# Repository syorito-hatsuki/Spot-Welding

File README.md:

# Spot Welding

## Description
Simple Arduino spot welding controller

## Requirements
* [VSCode](https://code.visualstudio.com)
* [PlatformIO Extension](https://marketplace.visualstudio.com/items?itemName=platformio.platformio-ide)

## Structure 
* `.vscode - Visual Studio Code configs for current project`
* `include - PlatformIO folder for C++ header files`
* `lib - PlatformIO folder for downloaded libraries`
* `pcb - KiCAD files (schematic, pcb, components)`
* `src - Source code for Arduino`
* `test - Unit test folder`

## Licence
[MIT License](https://github.com/syorito-hatsuki/Spot-Welding/blob/master/LICENSE)

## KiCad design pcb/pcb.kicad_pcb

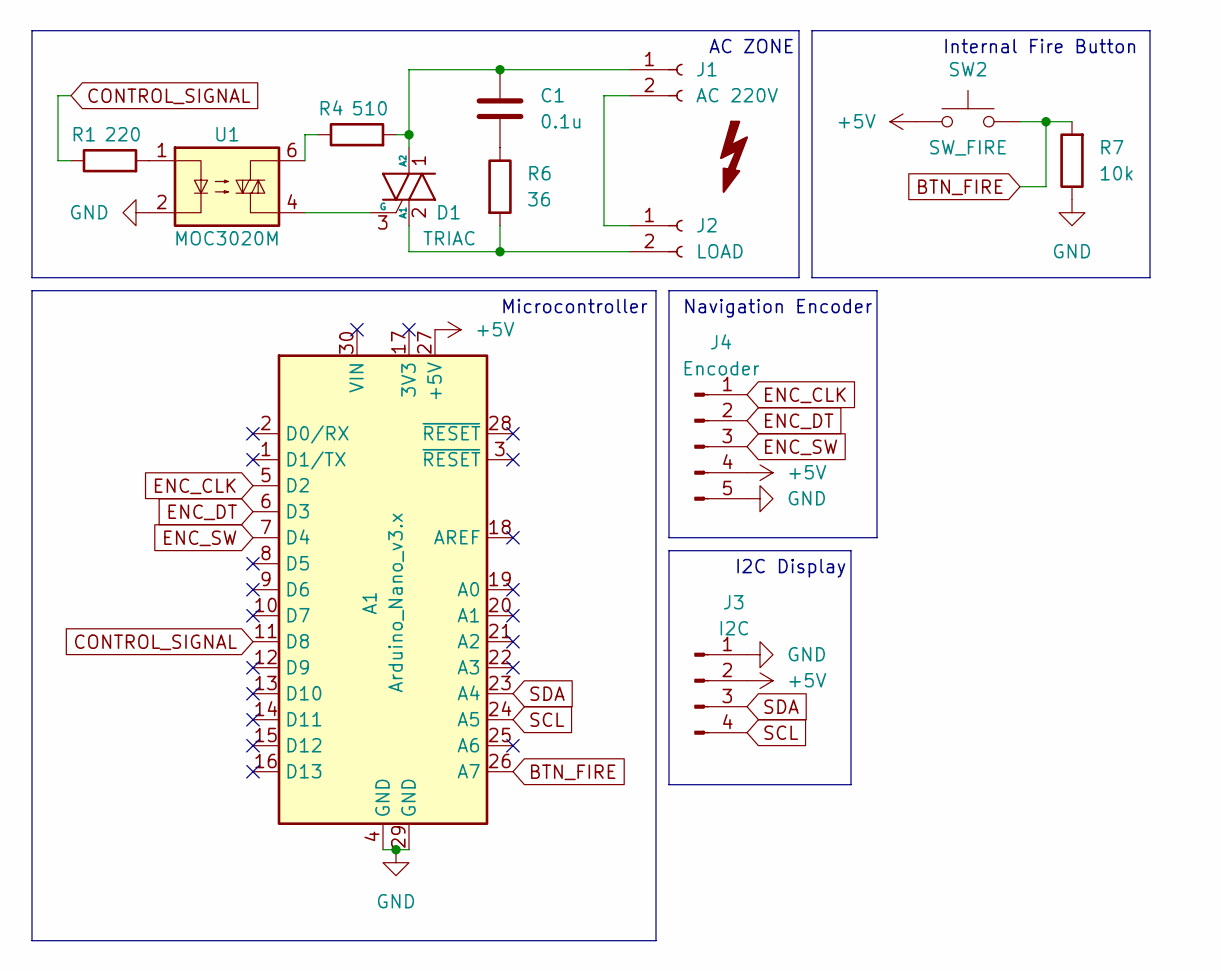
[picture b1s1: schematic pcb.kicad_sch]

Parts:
A1: Arduino_Nano_v3.x; Arduino_Nano
C1: 0.1u; C_Rect_L18.0mm_W6.0mm_P15.00mm_FKS3_FKP3
D1: TRIAC; TO-220-3_Vertical
J1: AC 220V; TerminalBlock_bornier-2_P5.08mm
J2: LOAD; TerminalBlock_bornier-2_P5.08mm
J3: I2C; PinHeader_1x04_P2.54mm_Vertical
J4: Encoder; PinHeader_1x05_P2.54mm_Vertical
R1: 220; R_Axial_DIN0207_L6.3mm_D2.5mm_P10.16mm_Horizontal
R4: 510; R_Axial_DIN0207_L6.3mm_D2.5mm_P10.16mm_Horizontal
R6: 36; R_Axial_DIN0207_L6.3mm_D2.5mm_P10.16mm_Horizontal
R7: 10k; R_Axial_DIN0207_L6.3mm_D2.5mm_P10.16mm_Horizontal
SW2: SW_FIRE; PinHeader_1x02_P2.54mm_Vertical
U1: MOC3020M; DIP-6_W7.62mm_LongPads

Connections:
+5V: A1.27 (+5V), J3.2, J4.4, SW2.1
BTN_FIRE: A1.26 (A7), R7.2, SW2.2
CONTROL_SIGNAL: A1.11 (D8), R1.1
ENC_CLK: A1.5 (D2), J4.1
ENC_DT: A1.6 (D3), J4.2
ENC_SW: A1.7 (D4), J4.3
GND: A1.4 (GND), A1.29 (GND), J3.1, J4.5, R7.1, U1.2
unnamed: C1.1, D1.1 (A2), J1.1, R4.2
unnamed: C1.2, R6.1
unnamed: D1.2 (A1), J2.2, R6.2
unnamed: D1.3 (G), U1.4
unnamed: J1.2, J2.1
unnamed: R1.2, U1.1
unnamed: R4.1, U1.6
SCL: A1.24 (A5), J3.4
SDA: A1.23 (A4), J3.3

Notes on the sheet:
AC ZONE
Navigation Encoder
I2C Display
Microcontroller
Internal Fire Button

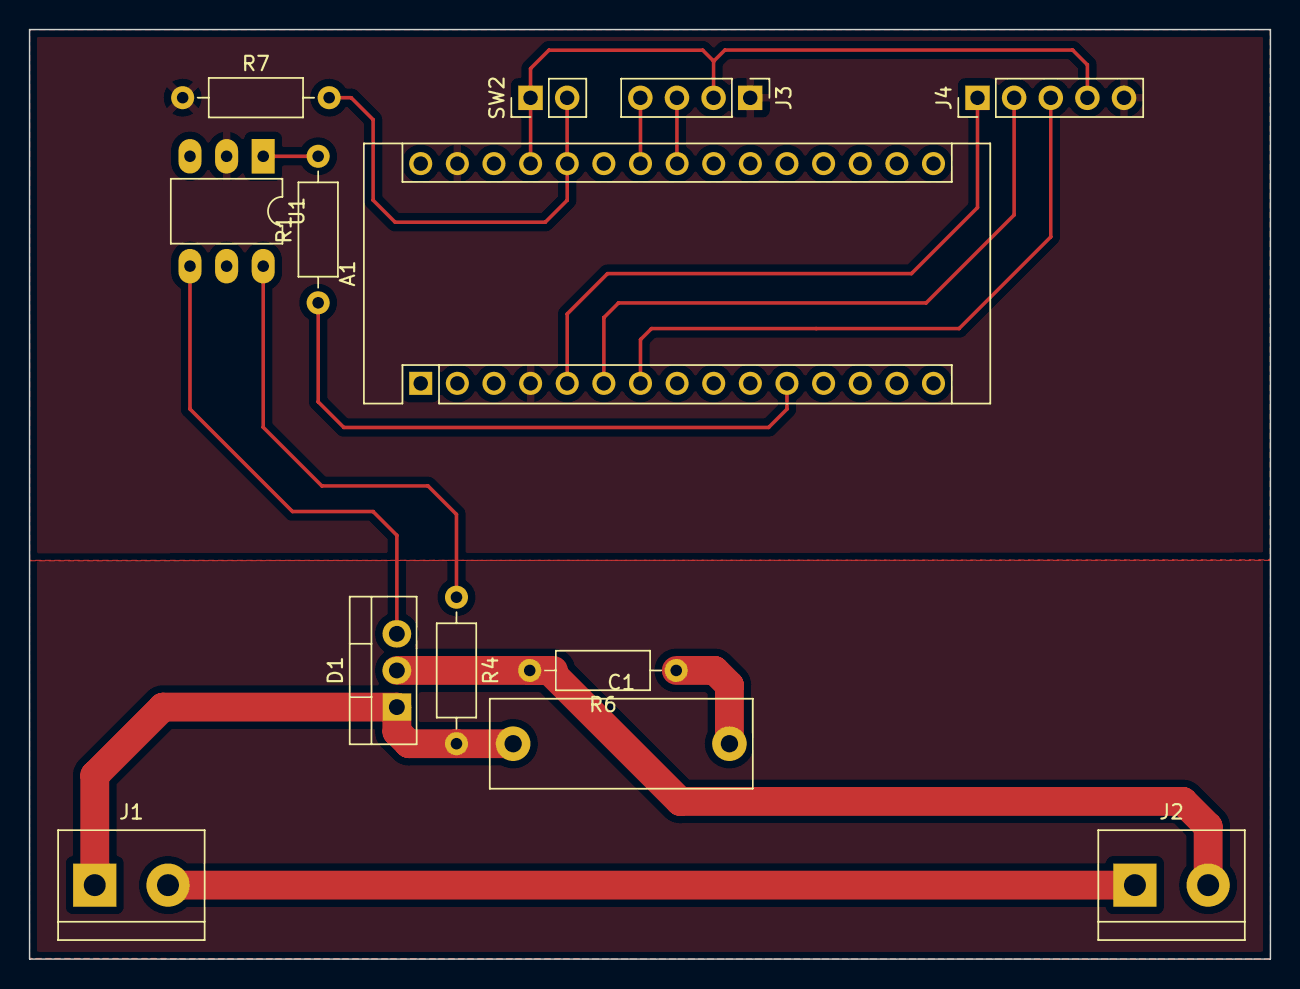
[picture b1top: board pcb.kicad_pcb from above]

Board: 2 copper layers, 86.1 x 64.5 mm, 13 parts (0 on the bottom side), 16 nets.

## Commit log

2021-08-10 init repo [0.0.1]
2021-08-11 Added settings saving
2022-06-20 SSH Test
2022-09-07 Added latest changes
